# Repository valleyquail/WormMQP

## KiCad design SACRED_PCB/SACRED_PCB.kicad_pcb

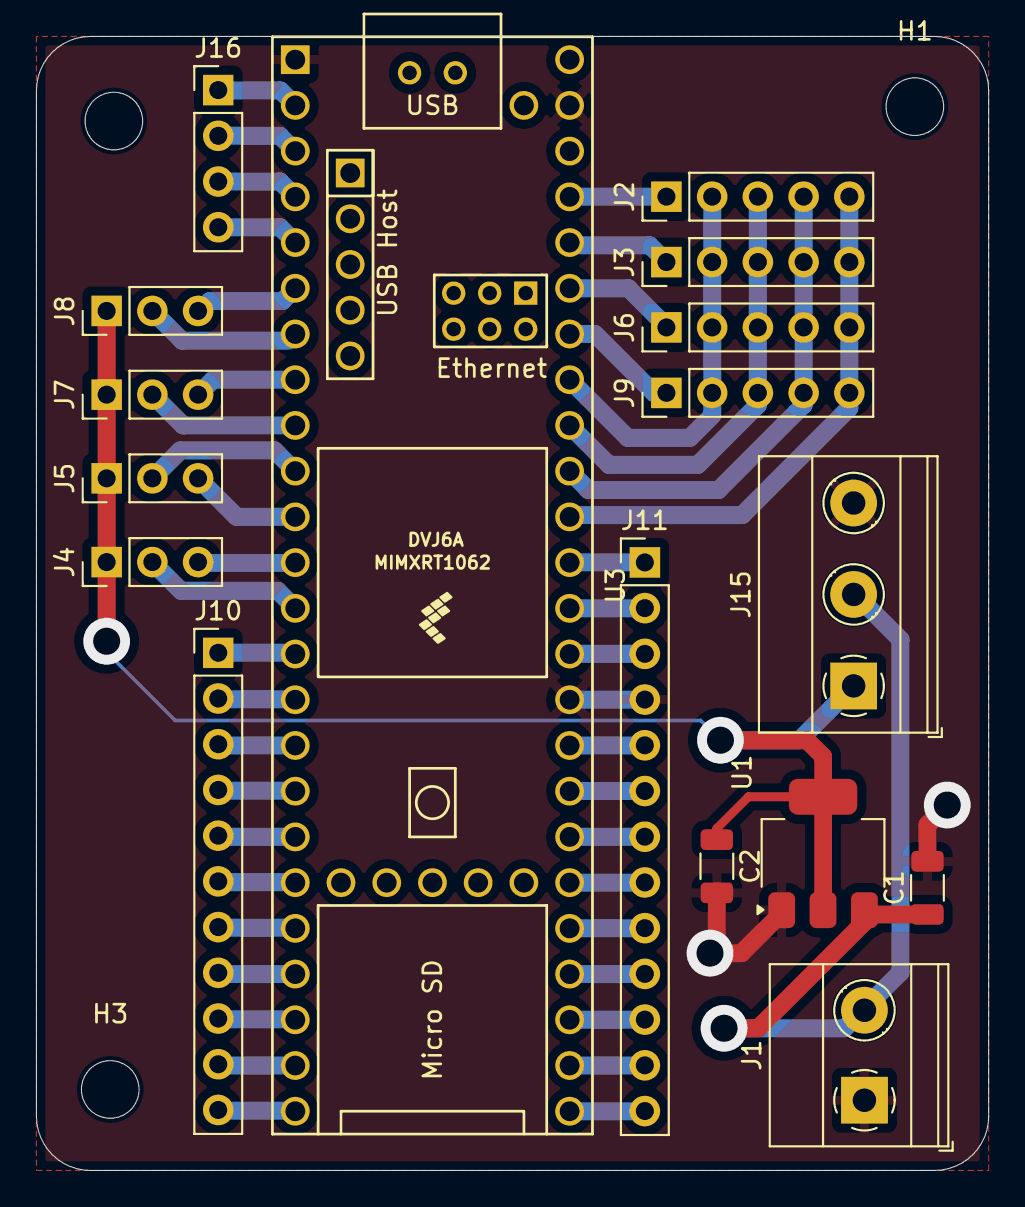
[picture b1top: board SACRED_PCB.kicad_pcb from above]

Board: 2 copper layers, 52.9 x 63.0 mm, 20 parts (0 on the bottom side), 46 nets.

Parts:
C1: 10uF; C_1206_3216Metric
C2: 22uF; C_1206_3216Metric
H1, H2, H3: MountingHole; MountingHole_3.2mm_M3
J1: Screw_Terminal_01x02; TerminalBlock_Phoenix_MKDS-1,5-2_1x02_P5.00mm_Horizontal
J2: Analog 0; PinHeader_1x05_P2.54mm_Vertical
J3: Analog 1; PinHeader_1x05_P2.54mm_Vertical
J4: Stepper 0; PinHeader_1x03_P2.54mm_Vertical
J5: Stepper 1; PinHeader_1x03_P2.54mm_Vertical
J6: Analog 2; PinHeader_1x05_P2.54mm_Vertical
J7: Stepper 2; PinHeader_1x03_P2.54mm_Vertical
J8: Stepper 3; PinHeader_1x03_P2.54mm_Vertical
J9: Analog 3; PinHeader_1x05_P2.54mm_Vertical
J10: Conn_01x11; PinHeader_1x11_P2.54mm_Vertical
J11: Conn_01x13; PinHeader_1x13_P2.54mm_Vertical
J15: Screw_Terminal_01x04; TerminalBlock_Phoenix_MKDS-1,5-3-5.08_1x03_P5.08mm_Horizont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
J16: Conn_01x04; PinHeader_1x04_P2.54mm_Vertical
U1: AMS1117-5.0; SOT-223-3_TabPin2
U3: Teensy4.1; Teensy41_2

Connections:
+5V: C2.1, J4.1, J5.1, J7.1, J8.1, J15.1, U1.2 (VO)
+12V: C1.1, J1.2, J15.2, U1.3 (VI)
/Analog_0: J2.1, U3.45 (23_A9_CRX1_MCLK1)
/Analog_1: J3.1, U3.44 (22_A8_CTX1)
/Analog_2: J6.1, U3.43 (21_A7_RX5_BCLK1)
/Analog_3: J9.1, U3.42 (20_A6_TX5_LRCLK1)
/MUX_0: J2.2, J3.2, J6.2, J9.2, U3.41 (19_A5_SCL)
/MUX_1: J2.3, J3.3, J6.3, J9.3, U3.40 (18_A4_SDA)
/MUX_2: J2.4, J3.4, J6.4, J9.4, U3.39 (17_A3_TX4_SDA1)
/MUX_3: J2.5, J3.5, J6.5, J9.5, U3.38 (16_A2_RX4_SCL1)
/Pin_0: J16.1, U3.2 (0_RX1_CRX2_CS1)
/Pin_1: J16.2, U3.3 (1_TX1_CTX2_MISO1)
/Pin_2: J16.3, U3.4 (2_OUT2)
/Pin_3: J16.4, U3.5 (3_LRCLK2)
/Pin_3v3: J10.2, U3.15 (3V3)
/Pin_12: J10.1, U3.14 (12_MISO_MQSL)
/Pin_13: J11.3, U3.35 (13_SCK_LED)
/Pin_14: J11.2, U3.36 (14_A0_TX3_SPDIF_OUT)
/Pin_15: J11.1, U3.37 (15_A1_RX3_SPDIF_IN)
/Pin_24: J10.3, U3.16 (24_A10_TX6_SCL2)
/Pin_25: J10.4, U3.17 (25_A11_RX6_SDA2)
/Pin_26: J10.5, U3.18 (26_A12_MOSI1)
/Pin_27: J10.6, U3.19 (27_A13_SCK1)
/Pin_28: J10.7, U3.20 (28_RX7)
/Pin_29: J10.8, U3.21 (29_TX7)
/Pin_30: J10.9, U3.22 (30_CRX3)
/Pin_31: J10.10, U3.23 (31_CTX3)
/Pin_32: J10.11, U3.24 (32_OUT1B)
/Pin_33: J11.13, U3.25 (33_MCLK2)
/Pin_34: J11.12, U3.26 (34_RX8)
/Pin_35: J11.11, U3.27 (35_TX8)
/Pin_36: J11.10, U3.28 (36_CS)
/Pin_37: J11.9, U3.29 (37_CS)
/Pin_38: J11.8, U3.30 (38_CS1_IN1)
/Pin_39: J11.7, U3.31 (39_MISO1_OUT1A)
/Pin_40: J11.6, U3.32 (40_A16)
/Pin_41: J11.5, U3.33 (41_A17)
/Stepper_0_DIR: J4.2, U3.13 (11_MOSI_CTX1)
/Stepper_0_STEP: J4.3, U3.12 (10_CS_MQSR)
/Stepper_1_DIR: J5.3, U3.11 (9_OUT1C)
/Stepper_1_STEP: J5.2, U3.10 (8_TX2_IN1)
/Stepper_2_DIR: J7.3, U3.8 (6_OUT1D)
/Stepper_2_STEP: J7.2, U3.9 (7_RX2_OUT1A)
/Stepper_3_DIR: J8.3, U3.6 (4_BCLK2)
/Stepper_3_STEP: J8.2, U3.7 (5_IN2)
GND: C1.2, C2.2, J1.1, J11.4, J15.3, U1.1 (GND), U3.1 (GND), U3.34 (GND), U3.47 (GND)

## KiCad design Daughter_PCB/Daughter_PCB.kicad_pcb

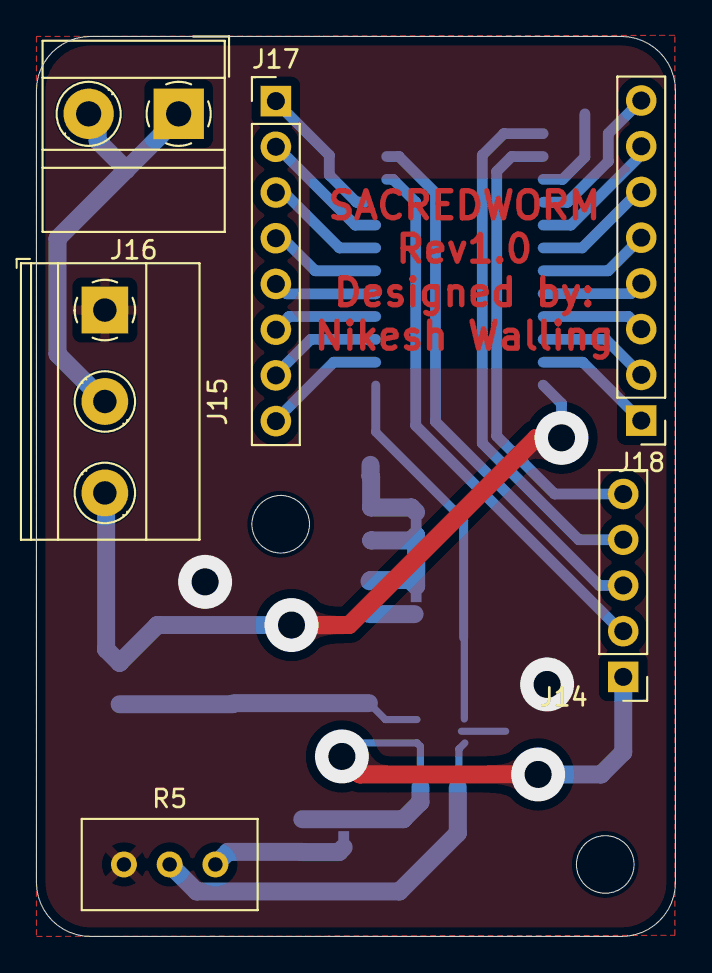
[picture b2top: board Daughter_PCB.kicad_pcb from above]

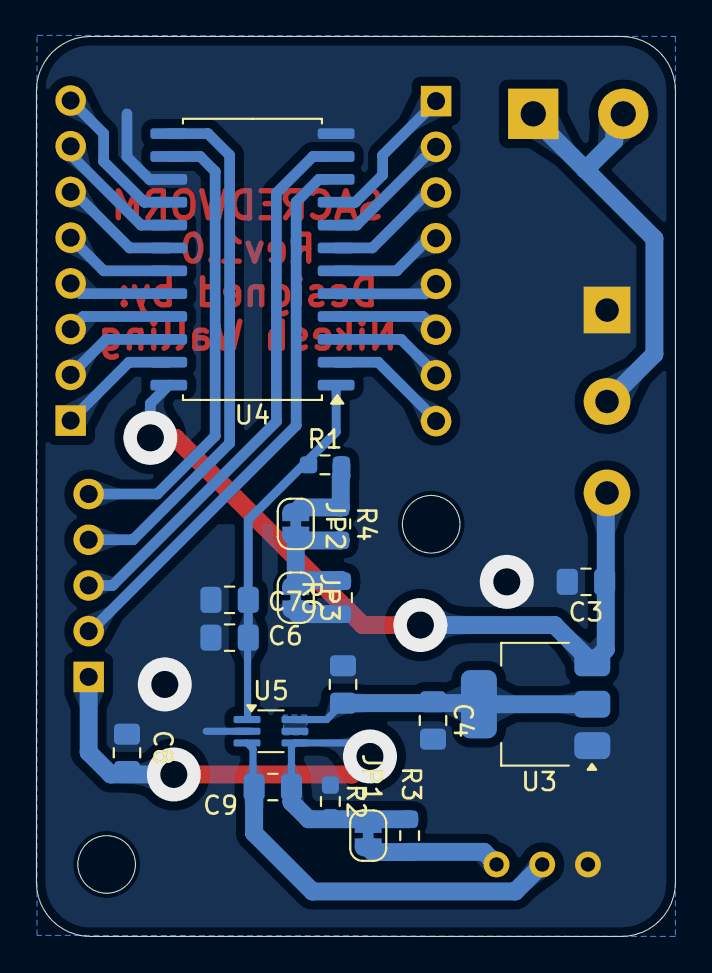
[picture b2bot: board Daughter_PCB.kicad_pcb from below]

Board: 2 copper layers, 35.5 x 50.0 mm, 26 parts (18 on the bottom side), 30 nets.

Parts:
C3, C4, C6, C8: 10uF; C_0805_2012Metric_Pad1.18x1.45mm_HandSolder
C5, C7: 100nF; C_0805_2012Metric_Pad1.18x1.45mm_HandSolder
C9: 1pF; C_0805_2012Metric_Pad1.18x1.45mm_HandSolder
H4, H5: MountingHole; MountingHole_3.2mm_M3
J14: Analog 0; PinHeader_1x05_P2.54mm_Vertical
J15: Screw_Terminal_01x04; TerminalBlock_Phoenix_MKDS-1,5-3-5.08_1x03_P5.08mm_Horizont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
J16: Screw_Terminal_01x02; TerminalBlock_MetzConnect_Type011_RT05502HBWC_1x02_P5.00mm_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
J17, J18: Conn_01x08; PinHeader_1x08_P2.54mm_Vertical
JP1, JP2, JP3: Solder _Bridge; SolderJumper-2_P1.3mm_Bridged_RoundedPad1.0x1.5mm
R1, R3, R4, R6: 100k; R_0603_1608Metric_Pad0.98x0.95mm_HandSolder
R2: 10k; R_0603_1608Metric_Pad0.98x0.95mm_HandSolder
R5: R_Trim; Potentiometer_Bourns_3296W_Vertical
U3: AMS1117-3.3; SOT-223-3_TabPin2
U4: CD74HCT4067QM96Q; SOIC-24W_7.5x15.4mm_P1.27mm
U5: OPA607Q1; SOT-363_SC-70-6_Handsoldering

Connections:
+3.3V: C4.1, C5.2, U3.2 (VO), U5.5 (~DIS), U5.6 (V+)
+5V: C3.1, J15.3, U3.3 (VI), U4.24 (VCC)
+12V: J15.2, J16.1, J16.2
/Analog_0: C8.1, C9.2, J14.1, JP1.1 (A), R2.2, R3.1, U5.4
/MUX_0: J14.2, U4.10 (S0)
/MUX_1: J14.3, U4.11 (S1)
/MUX_2: J14.5, U4.14 (S2)
/MUX_3: J14.4, U4.13 (S3)
GND: C3.2, C4.2, C5.1, C6.2, C7.2, C8.2, J15.1, JP3.1 (A), R2.1, R5.3, R6.2, U3.1 (GND), U4.12 (GND), U4.15 (~E), U5.2 (V-)
unnamed: J17.1, U4.9 (I0)
unnamed: J17.2, U4.8 (I1)
unnamed: J17.3, U4.7 (I2)
unnamed: J17.4, U4.6 (I3)
unnamed: J17.5, U4.5 (I4)
unnamed: J17.6, U4.4 (I5)
unnamed: J17.7, U4.3 (I6)
unnamed: J17.8, U4.2 (I7)
unnamed: J18.1, U4.23 (I8)
unnamed: J18.2, U4.22 (I9)
unnamed: J18.3, U4.21 (I10)
unnamed: J18.4, U4.20 (I11)
unnamed: J18.5, U4.19 (I12)
unnamed: J18.6, U4.18 (I13)
unnamed: J18.7, U4.17 (I14)
unnamed: J18.8, U4.16 (I15)
unnamed: JP1.2 (B), R3.2, R5.1
unnamed: JP2.1 (A), JP3.2 (B), R4.2, R6.1
unnamed: JP2.2 (B), R1.2, R4.1
unnamed: C6.1, C7.1, R1.1, U4.1 (COM), U5.1 (+)
unnamed: C9.1, R5.2, U5.3 (-)

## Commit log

2024-10-21 Initial
2024-10-28 Squashing the initial commits
2024-10-28 Add files via upload
    files from 10/26
2024-10-31 More prints tracking
2024-11-12 stepper test works
2024-11-20 accel stepper works
2024-12-10 More progress
2024-12-13 cycle test code
2024-12-13 added some data analysis
2025-01-10 Add files via upload
    Added first draft of schematic
2025-01-10 Footprint
2025-01-17 more graphing
2025-01-23 new position tester
2025-01-23 save data
2025-01-23 PCB schematic and a bunch of other stuff
2025-01-24 minor change
2025-01-24 a bit of data
2025-01-24 save
2025-01-24 sd card
2025-01-28 Working graphing and final schematic
2025-01-28 Visualizing sensor edges wrong
2025-01-28 Graphing the strain sides
2025-01-29 new cycle testing
2025-02-05 new data vis
2025-02-11 Deep clone
2025-02-12 Trying to fix math
2025-02-13 save all data collected, basic model
2025-02-13 Proper arm generation and PCB progress
2025-02-13 Really shitty faces
2025-02-17 PCB Rev 0.1
2025-02-17 Gitignore
2025-02-17 Move wormbot python
2025-02-17 PCB with rivets
2025-02-18 fk is almost there, the base needs to be fixed and some parts are squishing weird
2025-02-18 uhh progress maybe
2025-02-20 new data
2025-02-21 base is grounded, but geometry is warping
2025-02-25 Saving changes
2025-02-25 Saving more
2025-03-03 Redid the analog multiplexer
2025-03-05 saving data
2025-03-05 save data again
2025-03-06 Cleaning
2025-04-03 working 3axis motion
2025-04-16 added DH
